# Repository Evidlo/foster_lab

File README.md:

# foster_run
Script for running mountainsort and mountainview on a single epoch.  Run inside epoch directory containing .rec file

#### Installation
Symlink to `~/bin` and add to your PATH
``` sh
mkdir ~/bin
ln -s $(realpath foster_run) ~/bin
echo "export PATH=$PATH:$HOME/bin"
```

#### Usage
```
foster_run build
```

Generates .mda files in `output.filtered/`, `output.whitened/`, `output.firings/` directories.  `output.exported/` must exist already.  Delete each directory to rerun step.

```
foster_run build REC_FILE
```

Same as previous step, but also generates `output.exported/` directory.

```
foster_run view FIRINGS_MDA_FILE
```

Runs qt-mountainview on files generated on build step

# led_array
Kicad files for tracking board

# python
Simple python program for extracting offsets and total duration from output of Trodes `exporttime` command

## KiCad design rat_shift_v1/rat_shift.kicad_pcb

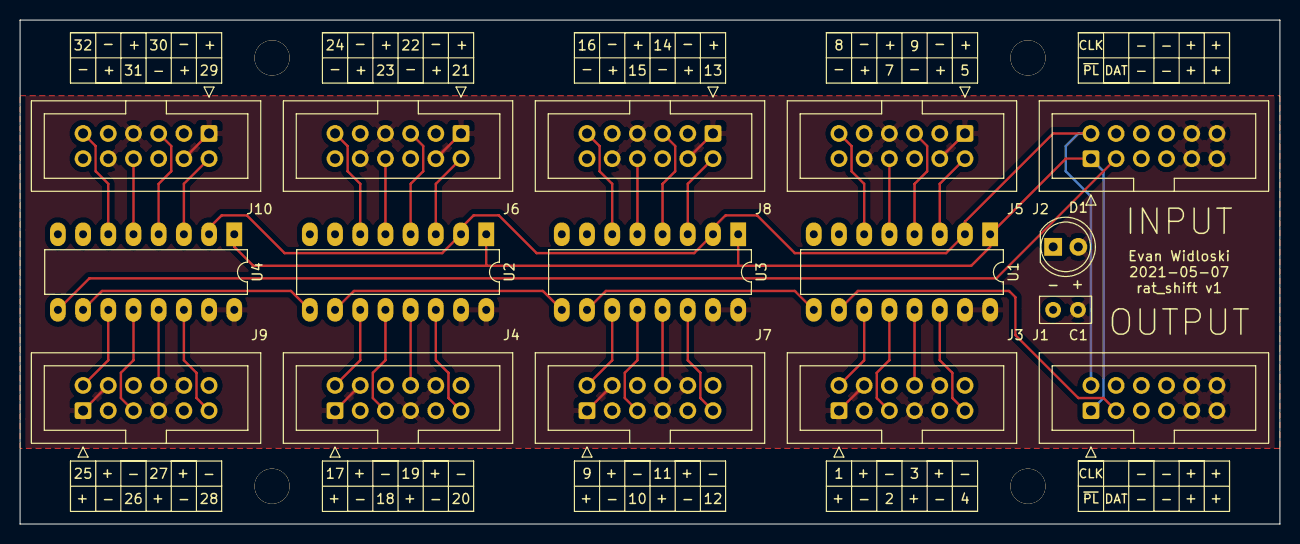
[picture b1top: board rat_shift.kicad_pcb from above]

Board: 2 copper layers, 127.0 x 50.8 mm, 16 parts (0 on the bottom side), 41 nets.

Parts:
C1: C; C_Disc_D5.0mm_W2.5mm_P2.50mm
D1: LED; LED_D5.0mm
J1, J2, J3, J4, J5, J6, J7, J8, J9, J10: Conn_01x12; IDC-Header_2x06_P2.54mm_Vertical
U1, U2, U3, U4: 74LS165; DIP-16_W7.62mm_LongPads

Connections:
+3V3: C1.1, D1.2, J1.9, J1.10, J1.11, J1.12, J2.9, J2.10, J2.11, J2.12, J3.1, J3.4, J3.7, J3.10, J4.1, J4.4, J4.7, J4.10, J5.1, J5.4, J5.7, J5.10, J6.1, J6.4, J6.7, J6.10, J7.1, J7.4, J7.7, J7.10, J8.1, J8.4, J8.7, J8.10, J9.1, J9.4, J9.7, J9.10, J10.1, J10.4, J10.7, J10.10, U1.15, U1.16, U2.15, U2.16, U3.15, U3.16, U4.15, U4.16
/CLK: J1.2, J2.2, U1.2, U2.2, U3.2, U4.2
/DAT_IN: J1.3, U1.10
/DAT_OUT: J2.3, U4.9
/OUT1: U1.9, U3.10
/OUT2: U2.10, U3.9
/OUT3: U2.9, U4.10
/PIR1: J3.2, U1.11
/PIR2: J3.5, U1.12
/PIR3: J3.8, U1.13
/PIR4: J3.11, U1.14
/PIR5: J5.2, U1.3
/PIR6: J5.5, U1.4
/PIR7: J5.8, U1.5
/PIR8: J5.11, U1.6
/PIR9: J7.2, U3.11
/PIR10: J7.5, U3.12
/PIR11: J7.8, U3.13
/PIR12: J7.11, U3.14
/PIR13: J8.2, U3.3
/PIR14: J8.5, U3.4
/PIR15: J8.8, U3.5
/PIR16: J8.11, U3.6
/PIR17: J4.2, U2.11
/PIR18: J4.5, U2.12
/PIR19: J4.8, U2.13
/PIR20: J4.11, U2.14
/PIR21: J6.2, U2.3
/PIR22: J6.5, U2.4
/PIR23: J6.8, U2.5
/PIR24: J6.11, U2.6
/PIR25: J9.2, U4.11
/PIR26: J9.5, U4.12
/PIR27: J9.8, U4.13
/PIR28: J9.11, U4.14
/PIR29: J10.2, U4.3
/PIR30: J10.5, U4.4
/PIR31: J10.8, U4.5
/PIR32: J10.11, U4.6
/~PL: J1.1, J2.1, U1.1, U2.1, U3.1, U4.1
GND: C1.2, D1.1, J1.5, J1.6, J1.7, J1.8, J2.5, J2.6, J2.7, J2.8, J3.3, J3.6, J3.9, J3.12, J4.3, J4.6, J4.9, J4.12, J5.3, J5.6, J5.9, J5.12, J6.3, J6.6, J6.9, J6.12, J7.3, J7.6, J7.9, J7.12, J8.3, J8.6, J8.9, J8.12, J9.3, J9.6, J9.9, J9.12, J10.3, J10.6, J10.9, J10.12, U1.8, U2.8, U3.8, U4.8

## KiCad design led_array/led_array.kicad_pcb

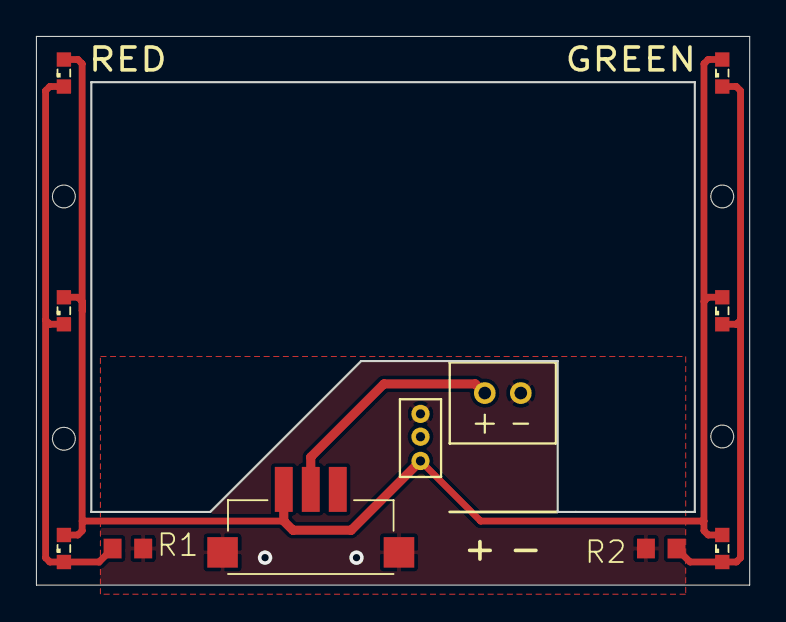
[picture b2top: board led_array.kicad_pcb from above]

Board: 2 copper layers, 39.6 x 30.4 mm, 15 parts (0 on the bottom side), 5 nets.

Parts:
GREEN1, GREEN3, GREEN3#2: LED_ESML0603; LED_SML0603
MH1, MH2, MH3, MH4: MountingHole; MountingHole_0-80
R1, R2: RR0603; R0603
RED1, RED2, RED3: LED_ESML0603; LED_SML0603
U$1: SWITCH_SLIDE_SPDT_0.4VA_28V
U$2: CONN_HEADER_MILLMAX_REC_3POS_0.5IN
U$3: JST_CONN_HEADER_PH_TOP_2POS_2MMJST_CONN_HEADER_PH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; JST_CONN_HEADER_PH_TOP_2POS_2MM

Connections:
/BATT: U$1.2, U$3.PWR
/GND: R1.2, R2.2, U$1.GND1, U$1.GND2, U$2.1, U$3.GND
/VCC: GREEN1.A, GREEN3.A, GREEN3#2.A, RED1.A, RED2.A, RED3.A, U$1.3, U$2.3
unnamed: GREEN1.C, GREEN3.C, GREEN3#2.C, R2.1
unnamed: R1.1, RED1.C, RED2.C, RED3.C

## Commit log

2018-08-15 add build script, led board, python script
2018-08-15 update readme, make executable
2018-08-23 update pcb
2018-08-24 fix build script
2021-05-10 add pir sensing boards
